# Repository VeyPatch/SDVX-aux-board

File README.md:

# SDVX-aux-board

### I lost the files for the original working board but recreated it from the working gerbers. While untested it should work as it's similar to the working design.

A replica of the aux board PWB111383270000 "sea horse" found in Sound Voltex cabs.

It makes use of a horizontal XH-4 female connector and an unidentified audio jack. For ease of manufacturing I decided to use a more common type of headphone jack (As I was also not able to identify the used jack). The official cycle time of that headphone jack is 5000 cycles. I also could not find any other brands which guaranteed a longer cycle time. While this is not a lot, the cheapness of the part will make replacing the jack a lot easier. The original metal bracket can still be used because the new audio jack is smaller in width.

| Item                 | part#              | lcsc part# | quantity |
|----------------------|--------------------|------------|----------|
| 3.5mm headphone jack | PJ-3910-7A         | C707257    | 1        |
| 1x4P XH 1 2.5mm      | S4B-XH-A-1(LF)(SN) | C163037    | 1        |

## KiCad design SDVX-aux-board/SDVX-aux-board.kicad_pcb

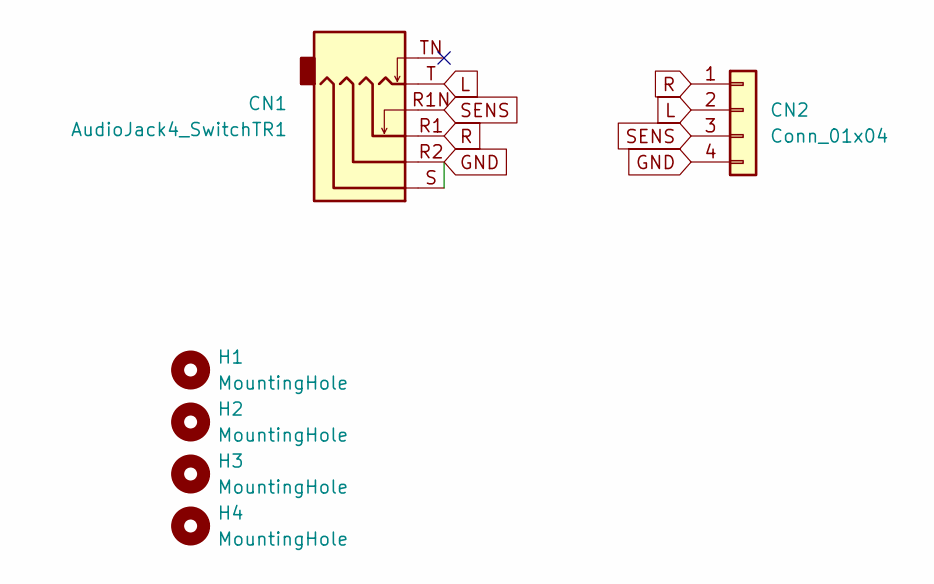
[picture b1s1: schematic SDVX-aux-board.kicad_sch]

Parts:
CN1: AudioJack4_SwitchTR1; PJ-3910-7A
CN2: Conn_01x04; JST_XH_S4B-XH-A_1x04_P2.50mm_Horizontal
H1, H2, H3, H4: MountingHole; MountingHole_3.5mm

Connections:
GND: CN1.R2, CN1.S, CN2.4
L: CN1.T, CN2.2
R: CN1.R1, CN2.1
SENS: CN1.R1N, CN2.3

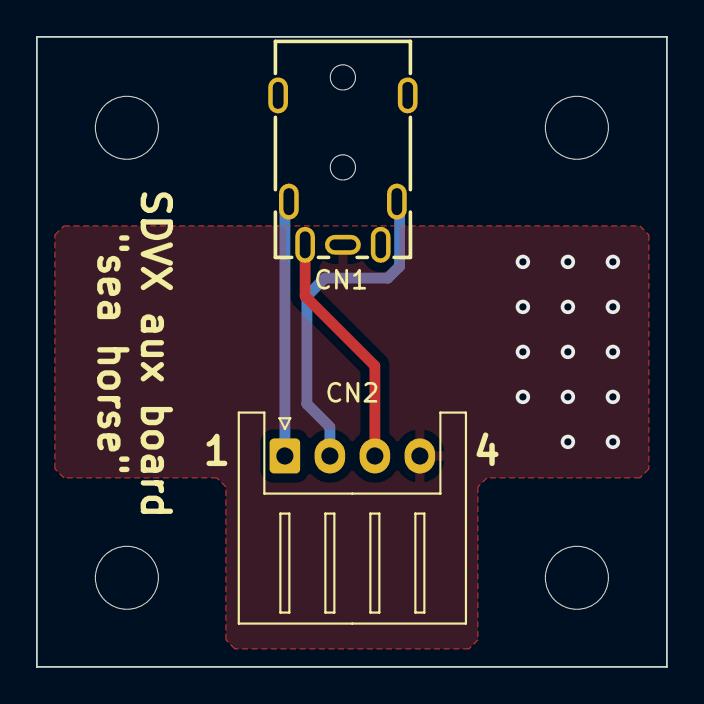
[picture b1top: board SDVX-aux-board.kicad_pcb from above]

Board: 2 copper layers, 35.0 x 35.0 mm, 6 parts (0 on the bottom side), 4 nets.

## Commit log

2023-02-06 Add pcb_layout
2023-02-07 Upload schematics, PCB and gerbers
2023-02-07 add image to readme
2024-10-22 Update to working design (kicad 8.0)
